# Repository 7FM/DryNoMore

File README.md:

# DryNoMore

TODO description, images, etc.

## Software

### Get the sources
- `git clone --recursive https://github.com/7FM/DryNoMore.git`
- Or `git clone https://github.com/7FM/DryNoMore.git` followed by `git submodule update --init --recursive`

### Dependencies
<details>
  <summary>For Debian:</summary>

```
apt install git git-lfs gcc make binutils cmake libssl-dev libboost-system-dev zlib1g-dev libyaml-cpp-dev 
```
Note that you will need `gcc-11` to compile the telegram bot, as it uses `std::bit_cast` (added in C++20).
Debian bullseye uses `gcc-10` by default and `g++-11` is currently only available in the testing channel.
Hence, you must add 
```
deb http://httpredir.debian.org/debian testing main contrib non-free
```
to `/etc/apt/sources.list`.
To avoid updating all packages to the testing channel create the file `/etc/apt/preferences.d/unstable-preferences` with the following content:
```
Package: *
Pin: release  a=testing
Pin-Priority: 100

Package: *
Pin: release a=unstable
Pin-Priority: 200
```
Then you can use `apt -t testing install gcc` to install `gcc-11`.
</details>

For NixOS see [`flake.nix`](./flake.nix).

### Compilation
- For the Arduino project simply use PlatformIO, i.e. through the [PlatformIO IDE](https://platformio.org/install/ide?install=vscode).
- For the Telegram Bot simply go into the folder `server/telegram_bot` and run `make`. On success a binary should be present at `server/telegram_bot/build/drynomore-telegram-bot`

### Configuration

<details>
  <summary>Configure the Arduino Project:</summary>

- all major settings are adjustable in the [`config.hpp`](./include/config.hpp)

TODO list options
</details>
<details>
  <summary>Configure the Telegram Bot:</summary>

- all major settings are adjustable though a YAML config file. As an example take a look at the [`example_config.yaml`](./server/telegram_bot/example_config.yaml).

TODO list options
</details>

## Hardware
### Known Flaws:
- v0.1:
    - Barrel Jack power input (J10) has swapped polarity.
- v0.2:
    - Main power consumption is caused by the W5500 Ethernet module

### Changelog:
#### v0.1 &rarr; v0.2:
- fix power input polarity
#### v0.2 &rarr; v0.3
- add mosfet to switch off the W5500 Ethernet module

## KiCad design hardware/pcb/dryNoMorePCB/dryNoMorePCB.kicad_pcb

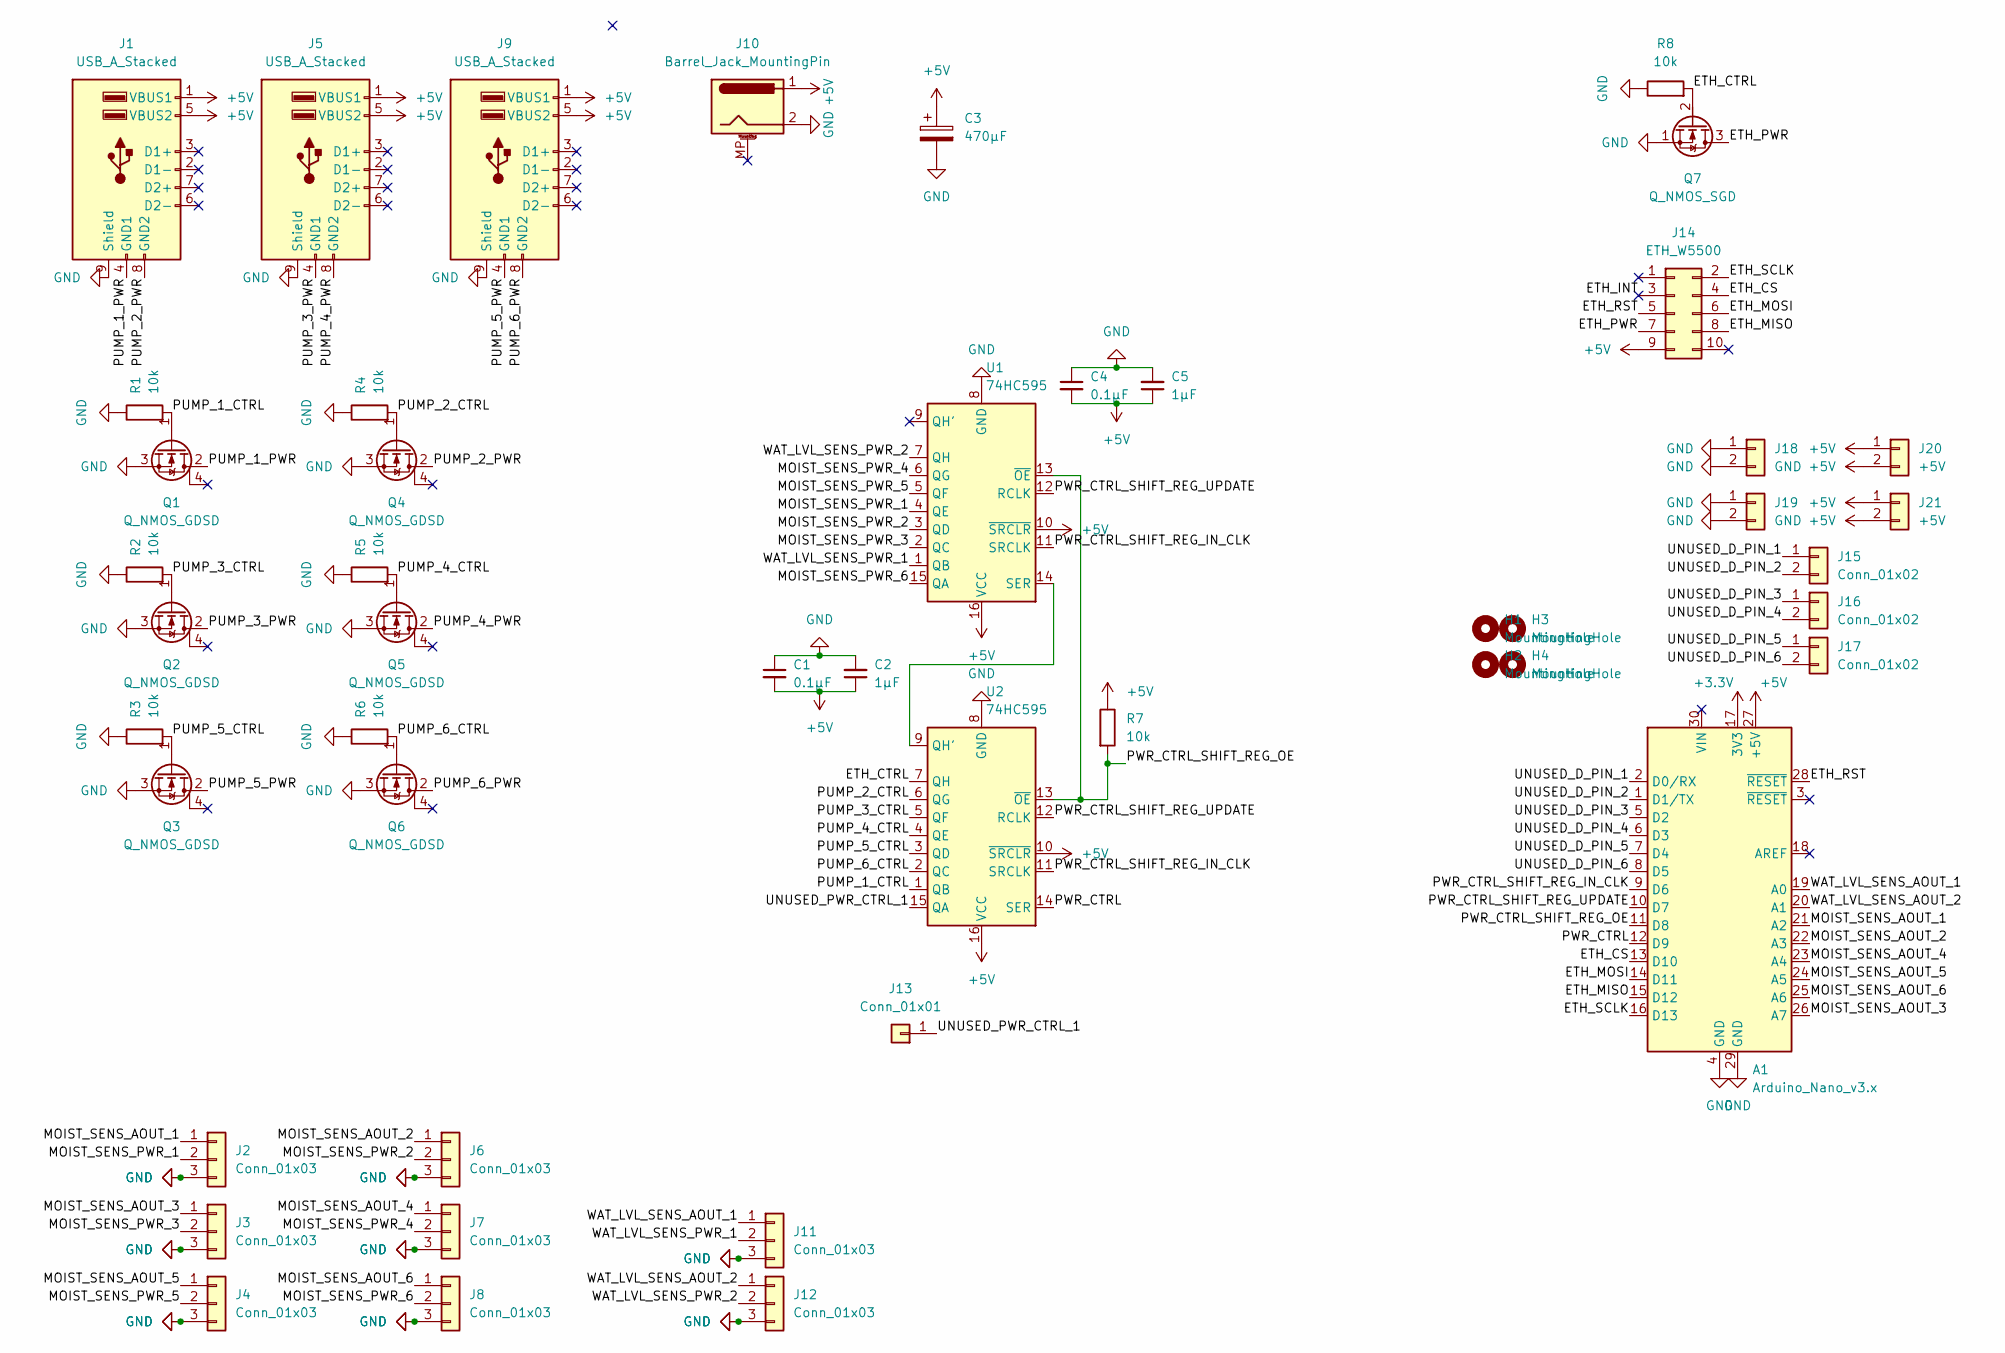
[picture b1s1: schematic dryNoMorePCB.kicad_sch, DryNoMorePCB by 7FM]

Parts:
A1: Arduino_Nano_v3.x; Arduino_Nano
C1, C4: 0.1µF; C_Disc_D3.8mm_W2.6mm_P2.50mm
C2, C5: 1µF; C_Rect_L4.0mm_W2.5mm_P2.50mm
C3: 470µF; CP_Radial_D8.0mm_P3.50mm
H1, H2, H3, H4: MountingHole; MountingHole_3.2mm_M3_DIN965
J1, J5, J9: USB_A_Stacked; USB_A_Wuerth_61400826021_Horizontal_Stacked
J2, J3, J4, J6, J7, J8, J11, J12: Conn_01x03; PinHeader_1x03_P2.54mm_Vertical
J10: Barrel_Jack_MountingPin; BarrelJack_Horizontal
J13: Conn_01x01; PinHeader_1x01_P2.54mm_Vertical
J14: ETH_W5500; PinSocket_2x05_P2.54mm_Vertical
J15, J16, J17: Conn_01x02; PinHeader_1x02_P2.54mm_Vertical
J18, J19: GND; PinHeader_1x02_P2.54mm_Vertical
J20, J21: +5V; PinHeader_1x02_P2.54mm_Vertical
Q1, Q2, Q3, Q4, Q5, Q6: Q_NMOS_GDSD; TO-220-3_Vertical
Q7: Q_NMOS_SGD; TO-92_Inline
R1, R2, R3, R4, R5, R6, R7: 10k; R_Axial_DIN0207_L6.3mm_D2.5mm_P7.62mm_Horizontal
R8: 10k; R_Axial_DIN0207_L6.3mm_D2.5mm_P2.54mm_Vertical
U1, U2: 74HC595; DIP-16_W7.62mm_Socket

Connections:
+3V3: A1.17 (3V3)
+5V: A1.27 (+5V), C1.2, C2.1, C3.1, C4.2, C5.1, J1.1 (VBUS1), J1.5 (VBUS2), J5.1 (VBUS1), J5.5 (VBUS2), J9.1 (VBUS1), J9.5 (VBUS2), J10.1, J14.9, J20.1, J20.2, J21.1, J21.2, R7.1, U1.10 (~SRCLR), U1.16 (VCC), U2.10 (~SRCLR), U2.16 (VCC); also elsewhere on the board
/ETH_CS: A1.13 (D10), J14.4
/ETH_CTRL: Q7.2 (G), R8.2, U2.7 (QH)
/ETH_INT: J14.3
/ETH_MISO: A1.15 (D12), J14.8
/ETH_MOSI: A1.14 (D11), J14.6
/ETH_PWR: J14.7, Q7.3 (D)
/ETH_RST: A1.28 (~RESET), J14.5
/ETH_SCLK: A1.16 (D13), J14.2
/MOIST_SENS_AOUT_1: A1.21 (A2), J2.1
/MOIST_SENS_AOUT_2: A1.22 (A3), J6.1
/MOIST_SENS_AOUT_3: A1.26 (A7), J3.1
/MOIST_SENS_AOUT_4: A1.23 (A4), J7.1
/MOIST_SENS_AOUT_5: A1.24 (A5), J4.1
/MOIST_SENS_AOUT_6: A1.25 (A6), J8.1
/MOIST_SENS_PWR_1: J2.2, U1.4 (QE)
/MOIST_SENS_PWR_2: J6.2, U1.3 (QD)
/MOIST_SENS_PWR_3: J3.2, U1.2 (QC)
/MOIST_SENS_PWR_4: J7.2, U1.6 (QG)
/MOIST_SENS_PWR_5: J4.2, U1.5 (QF)
/MOIST_SENS_PWR_6: J8.2, U1.15 (QA)
/PUMP_1_CTRL: Q1.1 (G), R1.2, U2.1 (QB)
/PUMP_1_PWR: J1.4 (GND1), Q1.2 (D); also elsewhere on the board
/PUMP_2_CTRL: Q4.1 (G), R4.2, U2.6 (QG)
/PUMP_2_PWR: J1.8 (GND2), Q4.2 (D); also elsewhere on the board
/PUMP_3_CTRL: Q2.1 (G), R2.2, U2.5 (QF)
/PUMP_3_PWR: J5.4 (GND1), Q2.2 (D); also elsewhere on the board
/PUMP_4_CTRL: Q5.1 (G), R5.2, U2.4 (QE)
/PUMP_4_PWR: J5.8 (GND2), Q5.2 (D); also elsewhere on the board
/PUMP_5_CTRL: Q3.1 (G), R3.2, U2.3 (QD)
/PUMP_5_PWR: J9.4 (GND1), Q3.2 (D); also elsewhere on the board
/PUMP_6_CTRL: Q6.1 (G), R6.2, U2.2 (QC)
/PUMP_6_PWR: J9.8 (GND2), Q6.2 (D); also elsewhere on the board
/PWR_CTRL: A1.12 (D9), U2.14 (SER)
/PWR_CTRL_SHIFT_REG_IN_CLK: A1.9 (D6), U1.11 (SRCLK), U2.11 (SRCLK)
/PWR_CTRL_SHIFT_REG_OE: A1.11 (D8), R7.2, U1.13 (~OE), U2.13 (~OE)
/PWR_CTRL_SHIFT_REG_UPDATE: A1.10 (D7), U1.12 (RCLK), U2.12 (RCLK)
/UNUSED_D_PIN_1: A1.2 (D0/RX), J15.1
/UNUSED_D_PIN_2: A1.1 (D1/TX), J15.2
/UNUSED_D_PIN_3: A1.5 (D2), J16.1
/UNUSED_D_PIN_4: A1.6 (D3), J16.2
/UNUSED_D_PIN_5: A1.7 (D4), J17.1
/UNUSED_D_PIN_6: A1.8 (D5), J17.2
/UNUSED_PWR_CTRL_1: J13.1, U2.15 (QA)
/WAT_LVL_SENS_AOUT_1: A1.19 (A0), J11.1
/WAT_LVL_SENS_AOUT_2: A1.20 (A1), J12.1
/WAT_LVL_SENS_PWR_1: J11.2, U1.1 (QB)
/WAT_LVL_SENS_PWR_2: J12.2, U1.7 (QH)
GND: A1.4 (GND), A1.29 (GND), C1.1, C2.2, C3.2, C4.1, C5.2, J1.9 (Shield), J2.3, J3.3, J4.3, J5.9 (Shield), J6.3, J7.3, J8.3, J9.9 (Shield), J10.2, J11.3, J12.3, J18.1, J18.2, J19.1, J19.2, Q1.3 (S), Q2.3 (S), Q3.3 (S), Q4.3 (S), Q5.3 (S), Q6.3 (S), Q7.1 (S), R1.1, R2.1, R3.1, R4.1, R5.1, R6.1, R8.1, U1.8 (GND), U2.8 (GND); also elsewhere on the board
unnamed: U1.14 (SER), U2.9 (QH')

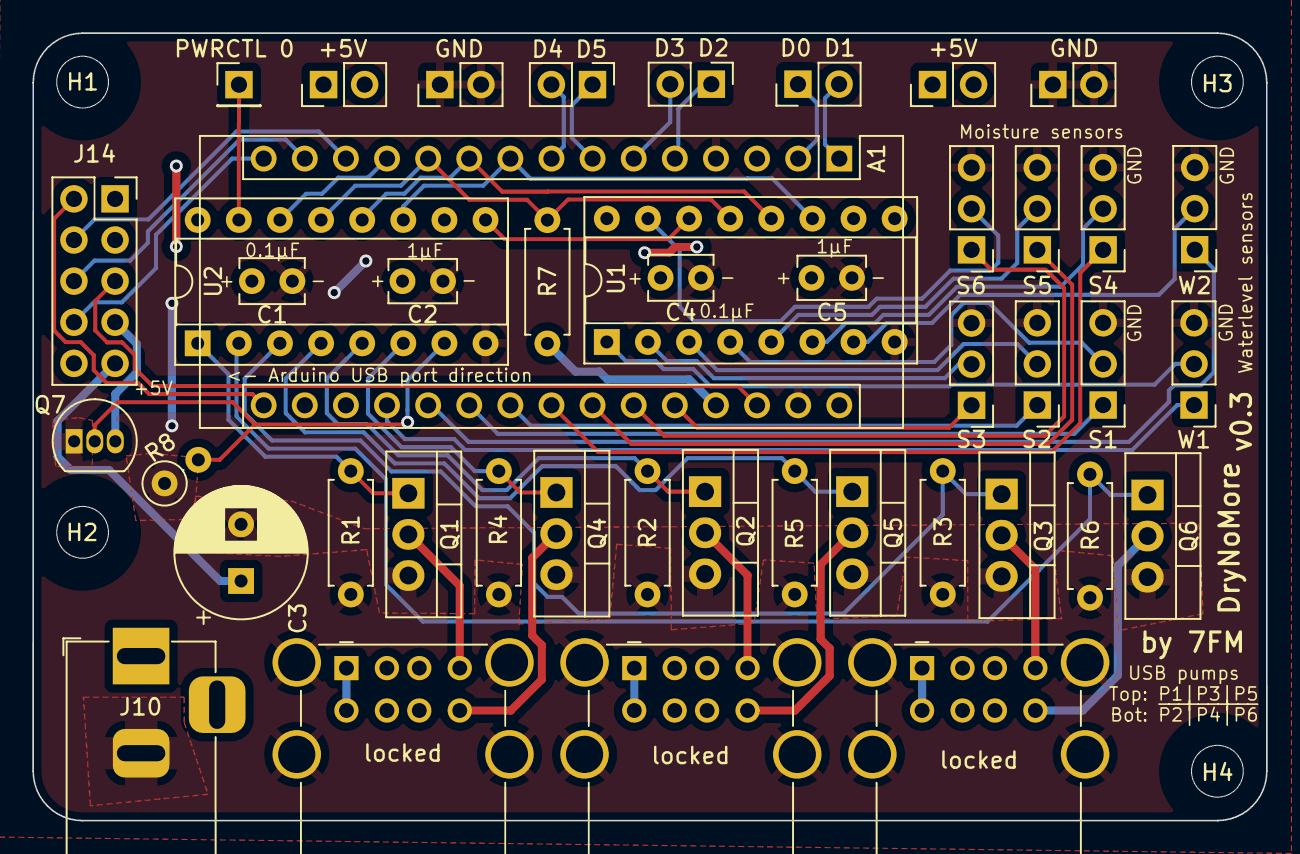
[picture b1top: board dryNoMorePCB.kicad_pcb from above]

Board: 2 copper layers, 76.2 x 48.6 mm, 48 parts (0 on the bottom side), 49 nets.

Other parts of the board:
locked: USB_A_Stacked; USB_A_Wuerth_61400826021_Horizontal_Stacked
locked#2, locked#3: USB_A_Stacked; USB_A_Wuerth_61400826021_Horizontal_Stacked

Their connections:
+5V: locked.1 (VBUS1), locked.5 (VBUS2), locked#2.1 (VBUS1), locked#2.5 (VBUS2), locked#3.1 (VBUS1), locked#3.5 (VBUS2); also elsewhere on the board
/PUMP_1_PWR: locked.4 (GND1); also elsewhere on the board
/PUMP_2_PWR: locked.8 (GND2); also elsewhere on the board
/PUMP_3_PWR: locked#3.4 (GND1); also elsewhere on the board
/PUMP_4_PWR: locked#3.8 (GND2); also elsewhere on the board
/PUMP_5_PWR: locked#2.4 (GND1); also elsewhere on the board
/PUMP_6_PWR: locked#2.8 (GND2); also elsewhere on the board
GND: locked.9 (Shield), locked#2.9 (Shield), locked#3.9 (Shield); also elsewhere on the board

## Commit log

2022-07-09 start with KiCAD pcb design
2022-07-09 add vscode extension recommendations
2022-07-09 add platformio project with first software draft
2022-07-09 add gitignore
2022-07-09 update gitignore
2022-07-09 hardware: add shift register & ethernet adapter
2022-07-10 more pcb progress
2022-07-12 more routing nightmares incoming
2022-07-16 almost done with the pcb
2022-07-16 update software to account for shift registers
2022-07-17 add circuit tree icon files
2022-07-17 more water level sensor code
2022-07-17 eth W5500: only connect 5V, add circuit tree icon to the backside
2022-07-19 fix missing filling +5V zone, USB pump silkscreen numbering
2022-07-19 remove board measurments from the silkscreen
2022-07-19 pcb: update pwr label
2022-07-20 add debug/setup modes
2022-07-24 adc measurement: invert percentage mapping
2022-07-24 add arduino framework patches to avoid division by zero, yet Serial output remains broken
2022-07-29 hardware: fix input voltage polarity (J10), pump version
2022-07-29 add README to document hardware revision changes
2022-07-30 progmem_string.hpp -> serial.hpp
2022-07-30 set a working serial speed
2022-07-31 more power saving stuff, fix pin initialization
2022-07-31 fix shiftreg power mappings
2022-07-31 improve sleep wakeup source rationale, move TODO
2022-08-01 introduce settings class
2022-08-05 add Ethernet as submodule
2022-08-05 first Ethernet lib patches
2022-08-05 start integrating Ethernet
2022-08-05 move serial baud rate setting
2022-08-05 start with telegram bot development
2022-08-05 nix flake env setup
2022-08-05 fix cmake setup
2022-08-06 introduce shared headers
2022-08-06 telegram bot will need threads
2022-08-06 we will need to change the SPI settings
2022-08-06 add SERIALreadBytes
2022-08-06 reformat
2022-08-06 add ts_queue
2022-08-06 telegram_bot: add tcp socket for communication with DryNoMore MCU
2022-08-07 nix: add gdb
2022-08-07 extend status struct for convenience reasons
2022-08-07 fix waterSensIdx calculation
2022-08-07 split up main & more progress with the telegram bot
2022-08-07 fix table generation
2022-08-07 improve table output
2022-08-07 generateTable: add multiline support
2022-08-07 main: extract adc measurement code
2022-08-07 add skipBitmap
2022-08-07 main: keep track of status, ensure that warnings/errors are only sent once per sensor
2022-08-07 main: introduce powerSavingSettings function
2022-08-07 formatting & improve comment
2022-08-07 use production mode by default
2022-08-07 telegram_bot: debug settings
2022-08-09 implement lan power down & energy saving modes
2022-08-09 move hardwareFailure flag into settings
2022-08-09 implement send messages
2022-08-09 update Ethernet submodule
2022-08-09 telegram_bot: extract table generation code
2022-08-10 fix compile
2022-08-11 telegram_bot: create some inline keyboards
2022-08-11 add missing initialization
2022-08-11 fix printMultiLineRow
2022-08-11 print hardware failure status too
2022-08-12 fix inline keyboards
2022-08-12 init new plants, add remove plants option
2022-08-12 add commit settings logic
2022-08-12 generateTable: allow controlling where whitespaces are printed
2022-08-13 fix min buttons
2022-08-13 fix wrong id
2022-08-13 only add as many edit pump buttons as active
2022-08-13 add remaining edit buttons
2022-08-14 optimize edit_moist action
2022-08-14 nix add yaml-cpp
2022-08-14 telegram_bot: add yaml config file support
2022-08-14 telegram_bot: add example_config.yaml
2022-08-14 config.hpp: adjust server port to match default settings of the telegram_bot
2022-08-14 config.hpp cleanup
2022-08-14 telegram_bot: check write results
2022-08-14 simplify updateSettings(...)
2022-08-15 fix typo
2022-08-15 README: add setup instructions
2022-08-15 README: use link to file
2022-08-15 make default water sensor mapping & skip plant settings configurable
2022-08-15 add missing newline
2022-08-18 generateStatusTable: handle UNDEFINED_LEVEL
2022-08-18 set resonable retry value
2022-08-18 send broadcast messages with markdown support
2022-08-18 send status message as markdown too
2022-08-23 telegram_bot: clip -100, -10, +10, +100 buttons at min/max values
2022-08-23 add option to configure a min. delay between irrigations
2022-08-23 cleanup
2022-08-25 git lfs track font files
2022-08-25 git lfs track freecad & stl files
2022-08-25 Add case CAD & STL files
2022-09-03 telegram bot: fix missing hardwareFailure message handling
2022-09-03 error msg: fix idx, move hwFailure code
2022-09-03 telegram bot: reduce status table width
2022-09-03 telegram bot: refine button texts
2022-09-03 fix warning, add missing changes
2022-09-03 report raw sensor data too
2022-09-03 report the unclamped adc measurement value!
2022-09-04 platformio: setup env to flash via usbasp
2022-09-05 fix compile for debug modes
2022-09-08 fix pin initialization
2022-09-08 dry_no_more_server: more error messages
2022-09-08 update submodule
2022-09-08 I hate exceptions
2022-09-08 early pin initialization to fully discharge capacitors
2022-09-10 ensure LEDs are off during sleep
2022-09-11 fix result code for warnings
2022-09-11 new hardware revision: add mosfet to switch off the ethernet module
2022-09-11 add todos
2022-09-11 use OUTPUT Low instead of INPUT_PULLUP
2022-09-11 more TODOs
2022-09-27 implement ETH module power switching
2022-09-27 use irrigation bursts & add settings to adjust them
2022-09-28 write & read last known settings to yaml config -> they are now persistent
2022-09-28 implicitly add missing SPI.begin()
2022-09-28 readd missing init
2022-09-28 telegram_bot: trying to reduce table width
2022-09-28 unify wording
2022-09-28 telegram_bot: handle SIGTERM signal for improved systemd integration
2022-10-01 telegram_bot: yaml config fix settings decoding
2022-10-01 allow burstDelay of 0
2022-10-01 update case design for HW rev 0.3 (untested)
2022-10-04 dry no more allow multiple requests?
2022-10-04 send HW failure message last
2022-10-04 resolve old todo
2022-10-05 change nmos from DGS to SGD pinout to match an 2N7000
2022-10-06 drynomore always send status messages notifications first
2022-10-06 add missing Ethernet powerup
2022-10-06 improve init order, only use INPUT_PULLUP for serial pins
2022-10-06 switch to input pullup for SPI signals to ensure ETH mosfet turns off
2022-10-08 more debug printing
2022-10-09 improve readability
2022-10-09 update tgbot submodule
2022-10-11 telegram bot: catch more exceptions
2022-10-26 keep track of time used for irrigation and adjust sleep time accordingly
2022-11-14 only send status reports on moisture changes
2023-05-02 add debug option to always send status updates
2023-05-02 telegram bot: fix compile
2023-05-02 bump settings version number
2023-05-02 check whether connecting to the client was successful
2023-05-02 add debug option
2023-05-08 more debug prints & add debug with normal cpu speed option
2023-05-08 simplyfy statusChanged checks & add another debug print
2023-05-08 autoformatting
2023-05-08 add debug prints of the send & received settings struct
2023-05-08 fix printing hex bytes
2023-05-08 remove prayers
2023-05-08 defaultSetting: enable debug mode
2023-05-08 updateSettings: handle client.read response properly, wait for data & more debug prints
2023-05-08 add a delay into the waiting loop
2023-05-08 dry_no_more_server: pass on all status updates in settings.debug mode!
2023-05-08 dry_no_more_server: add more debug prints
2023-05-08 give credit to IosFlagSaver
2023-05-08 disable debug by default
2023-06-01 check soil humidity only once before each irrigation burst, to reduce risk of misreadings during irrigation
2024-02-12 update tgbot-cpp submodule
2024-02-14 move location of shared headers
2024-02-14 properly package the telegram bot server
2024-02-14 nix: use packages attribute instead of defaultPackage
